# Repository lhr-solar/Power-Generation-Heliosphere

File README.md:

# :sunny: Heliosphere - Lighting automation control jig.

- [:sunny: Heliosphere - Lighting automation control jig.](#sunny-heliosphere---lighting-automation-control-jig)
  - [Repository Structure](#repository-structure)
  - [Maintainers](#maintainers)
  - [Versioning](#versioning)
  - [TODO](#todo)
    - [Documentation](#documentation)
    - [HW](#hw)
    - [SW](#sw)

---

## Repository Structure

- **datasheets** - contains datasheets for major components of the PCB.
- **docs** - contains documentation on how to build, test, and use the PCB.
- **fw** - contains fw that is loaded onto the PCB.
  - **tests** - test programs used to characterize and validate the PCB.
  - **src** - main program used to run the PCB.
  - **inc** - internally developed libraries specific for the PCB.
  - **lib** - third party libraries used by the PCB.
- **hw**
  - **footprints** - project specfic footprint association files for the PCB.
  - **models** - 3d .step files for the PCB 3d viewer.
  - **symbols** - project specific symbol files for the PCB.
  - **vX.Y.Z** - frozen versioning folder for PCB production files.
  - design files

---

## Maintainers

The current maintainer of this project is Matthew Yu as of 07/16/2023. His email
is [matthewjkyu@gmail.com](matthewjkyu@gmail.com).

Special thanks to Professor Gary Hallock, who supervised the development and
design of this project.

---

## Versioning

This PCB is on unified version `0.1.0`. Every time the schematic and/or layout
is updated, this version number should go up. We use [semantic
versioning](https://semver.org/) to denote between versions. See the
[changelog](./docs/CHANGELOG.md) for more details.

---

## TODO

### Documentation

- Update the following documents:
  - [Ordering and assembly](./docs/ORDERING_AND_ASSEMBLY.md)
  - [Testing](./docs/TESTING.md)
- Add datasheets for key components of the device.

### HW

- See [changelog 0.2.0rc](./docs/CHANGELOG.md#020rc-proposed) proposed changes to improve board cost, size.

### SW

- Regenerate code for MBED with proposed file structure.

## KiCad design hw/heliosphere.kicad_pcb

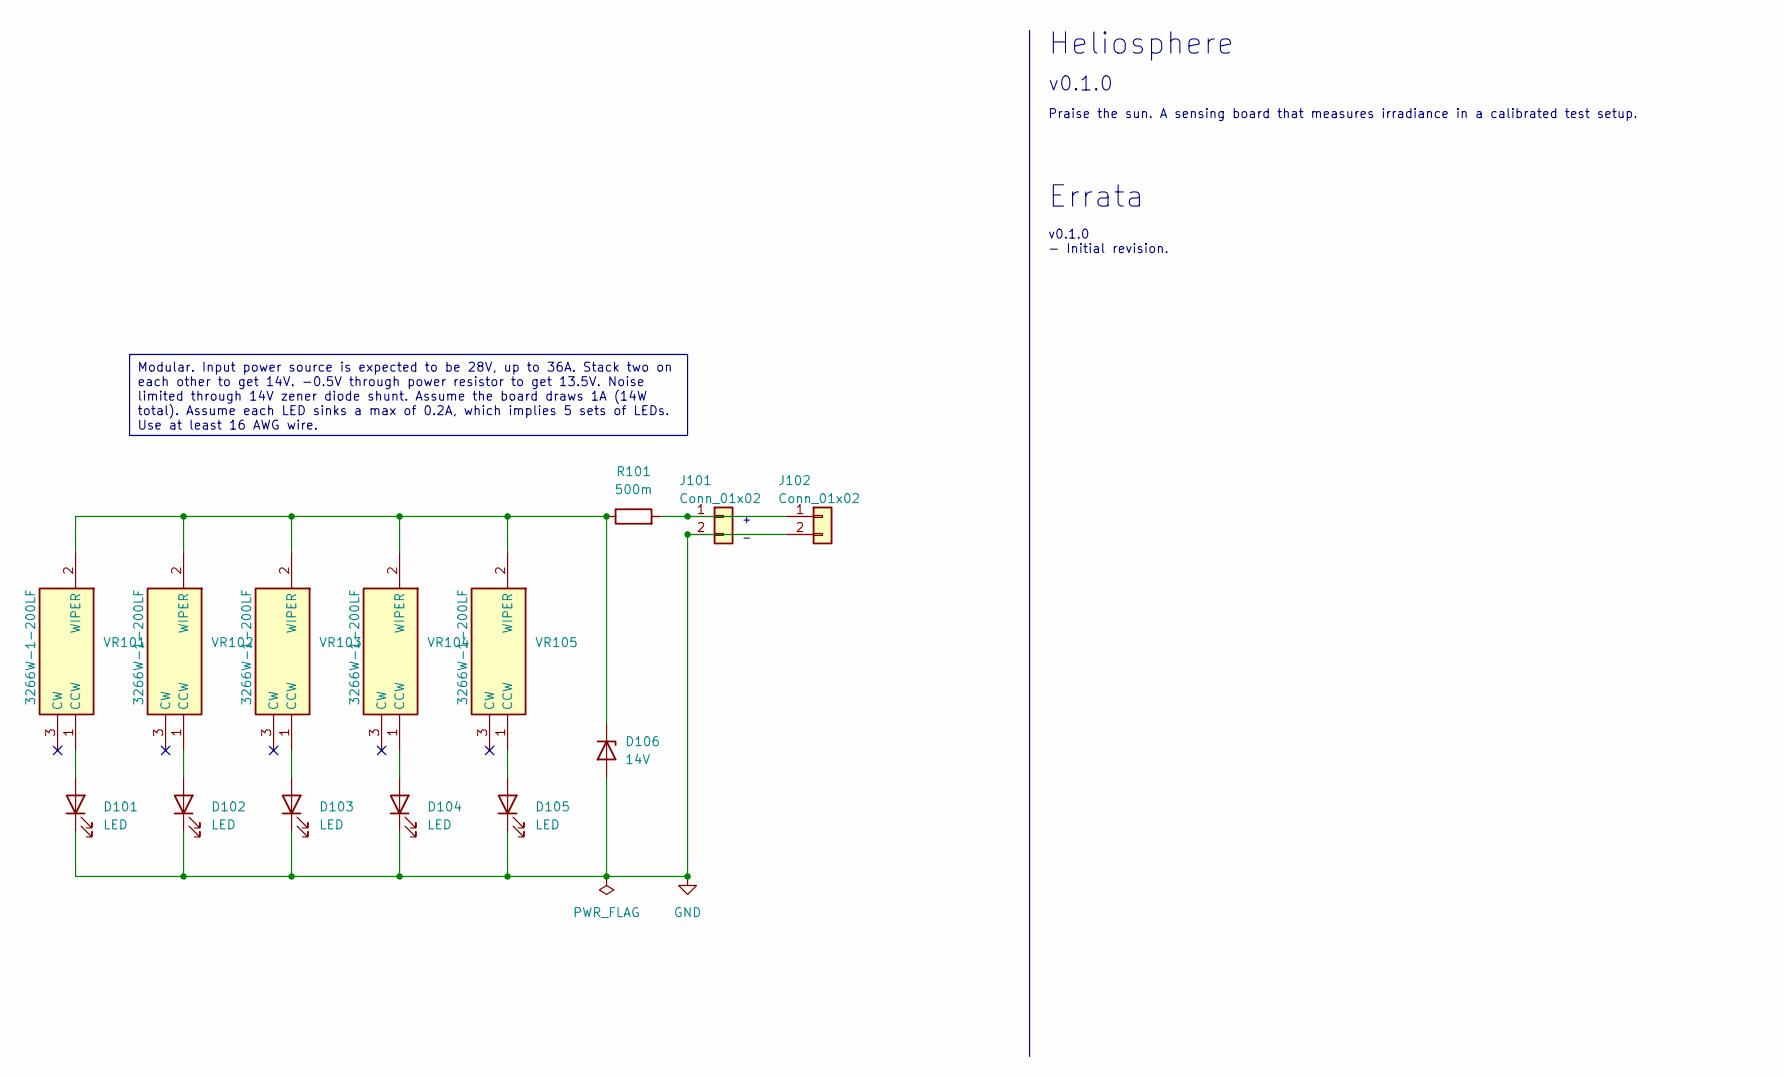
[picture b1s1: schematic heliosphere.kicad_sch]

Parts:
D101, D102, D103, D104, D105: LED; xishwon_led_bulb
D106: 14V; D_SMB-SMC_Universal_Handsoldering
J101, J102: Conn_01x02; SolderWire-2.5sqmm_1x02_P8.8mm_D2.4mm_OD4.4mm
R101: 500m; R_2512_6332Metric_Pad1.40x3.35mm_HandSolder
VR101, VR102, VR103, VR104, VR105: 3266W-1-200LF; bourns3266W_1_200LF

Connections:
GND: D101.1 (K), D102.1 (K), D103.1 (K), D104.1 (K), D105.1 (K), D106.2 (A), J101.2, J102.2
unnamed: D101.2 (A), VR101.1 (CCW)
unnamed: D102.2 (A), VR102.1 (CCW)
unnamed: D103.2 (A), VR103.1 (CCW)
unnamed: D104.2 (A), VR104.1 (CCW)
unnamed: D105.2 (A), VR105.1 (CCW)
unnamed: D106.1 (K), R101.1, VR101.2 (WIPER), VR102.2 (WIPER), VR103.2 (WIPER), VR104.2 (WIPER), VR105.2 (WIPER)
unnamed: J101.1, J102.1, R101.2

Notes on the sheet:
Modular. Input power source is expected to be 28V, up to 36A. Stack two on each other to get 14V. -0.5V through power resistor to get 13.5V. Noise limited through 14V zener diode shunt. Assume the board draws 1A (14W total). Assume each LED sinks a max of 0.2A, which implies 5 sets of LEDs. Use at 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
Heliosphere
Errata
v0.1.0 - Initial revision.
Praise the sun. A sensing board that measures irradiance in a calibrated test setup.
v0.1.0

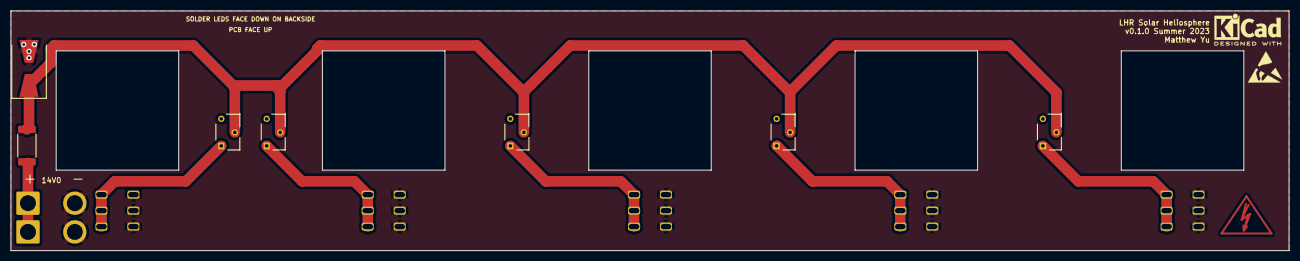
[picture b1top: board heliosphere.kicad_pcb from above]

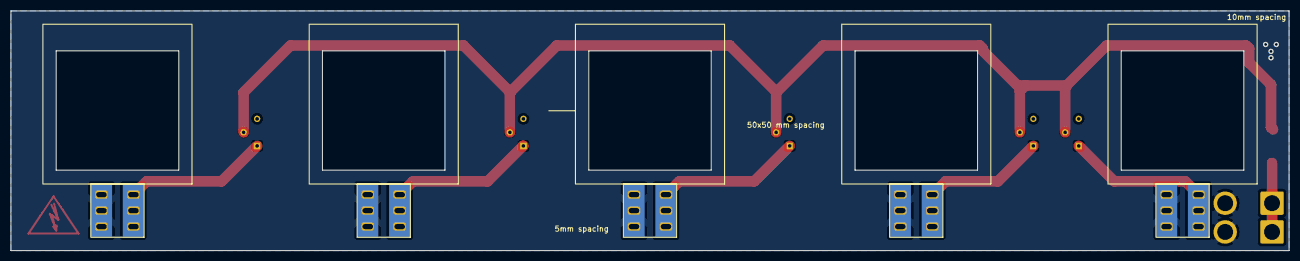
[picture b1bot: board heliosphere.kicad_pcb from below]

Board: 2 copper layers, 240.0 x 45.0 mm, 14 parts (5 on the bottom side), 8 nets.

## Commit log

2023-07-17 init commit for v0.1.0 of heliosphere.
2023-07-22 add screenshot
2023-08-01 footprint and schematic update
2023-08-19 swap trimpot for available one on mouser
2024-01-12 documentation
